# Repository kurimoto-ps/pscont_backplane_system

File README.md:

# pscont_backplane_system

**2マスターのクレート収容案**　[電源8 HP＋コンバータ36 HP＋チョッパ36 HP](backplane_board/mechanical/dual_master_crate/README.md) · [正面図・電源ベイの立体図・容量比較（PDF）](backplane_board/mechanical/dual_master_crate/dual_master_crate.pdf)

**比較元の1マスター機構案**　[6Uクレート・正面左16 HPの着脱式電源](backplane_board/mechanical/front_psu_16hp/README.md) · [3D組立・取付図（PDF）](backplane_board/mechanical/front_psu_16hp/PSCONT_front_PSU_views.pdf)

大型電源の三相PWMコンバータと2象限単相チョッパを制御するシステム。電流制御はSTM32H745XIH6、同期と指令配信は10M16DCF484I7Gで行う。2マスター案では各系統がPWM 6枚とDAC 1枚を担当する。下表のKiCad設計は先行する1マスター版。

| プロジェクト | 内容 |
|---|---|
| [backplane_board](backplane_board/README.md) | 受動バックプレーンの回路設計仕様。96差動対の割当、電源容量、保護、評価項目を含む。 |
| [16 ch DAC・4 HP化と盤内電源の検討](backplane_board/mechanical/dac_4hp/README.md) | 14共通スロット案。負荷別の電力、112対の割当、電源取付と背面保守のPDF・DXF・STEP。 |
| [KiCadプロジェクト](backplane_board/backplane_board.kicad_pro) | KiCad 10。全体結線、12 V保護、6Uマスタの160極2コネクタ、PWM 12スロットの階層回路図。 |
| [スロット結線表](backplane_board/slot_links.csv) | マスタ・スロット間の全96対。電気的に独立する正負ネットと終端位置。 |
| [回路図PDF](backplane_board/backplane_board.pdf) | A3、全22ページ。各スロットの実装部品番号を展開。 |
| [通販URL付きBOM](backplane_board/BOM.csv) | 1台分の購入部品と在庫掲載数。 |

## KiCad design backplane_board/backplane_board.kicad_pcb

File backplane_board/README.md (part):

# バックプレーン基板 回路設計仕様

**4 HPカード・前面着脱式電源の機構案**　[機構仕様・組立図・STEP・寸法DXF](mechanical/front_psu_16hp/README.md)。KiCad基板本体は先行する6 HP版。

[増設検討：16 ch DAC・4 HP共通スロット・電源取付（PDF／DXF／STEP）](mechanical/dac_4hp/README.md)。下のKiCad原図は比較元の12スロット版。

対象はマスタ1枚、三相PWMコンバータ用カード6枚、単相チョッパ用カード6枚を同時に実装できるバックプレーン。カード間の信号配線は受動式で、電源入口に逆接保護MOSFETを実装する。電力は電源入力容量を決めるための設計予算で、実測値・デバイス全動作条件での保証値とは区別する。

[全22ページの回路図PDF](backplane_board.pdf) · [KiCad 10プロジェクト](backplane_board.kicad_pro) · [購入用BOM](BOM.csv) · [端子対応表](slot_links.csv)

[KiCad基板・部品配置](backplane_board.kicad_pcb) · [部品配置と固定方法の図面（PDF 3ページ）](mechanical/placement_review.pdf) · [支持板・補強材の寸法と組付け](mechanical/README.md)

| PDF | 回路 | 接続先 |
|---|---|---|
| 1 | システム結線。1本のバスが16本の実配線を表す | マスタのJ2・J3から12個のPWMソケット |
| 2 | J1、F1、Q1、D1、R1、マスタ分岐F2 | 保護後の12 Vを全13分岐に供給 |
| 3–6 | J2、三相用6枚。3ページは給電・GNDと階層入口、4–6ページは各信号端子 | a列でC1/C2、b列でC3/C4、c列でC5/C6 |
| 7–10 | J3、チョッパ用6枚。7ページは給電・GNDと階層入口、8–10ページは各信号端子 | a列でH1/H2、b列でH3/H4、c列でH5/H6 |
| 11–22 | J11–J22。共通階層を物理スロットごとに展開 | 各48極、固有ヒューズF11–F22、測定点TP11–TP22 |

KiCadではプロジェクト一式を開く。BOMのHARTING型番には先頭にゼロがあるため、表計算ソフトへの取り込み時にMPN列を文字列として扱う。在庫欄には通販ページの掲載数、参照日、掲載情報の経過時間を記載した。

## 1. 実装単位と配線範囲

| 実装場所 | 主な部品・役割 |
|---|---|
| マスタ | STM32H745XIH6、SDRAM、MAX 10 10M16DCF484I7G、LVDS送受信器、基準クロック、トリップ集約・ラッチ。FMC16はSDRAM用。 |
| バックプレーン | マスタスロットM、ドータースロットC1–C6／H1–H6、電源入口と分岐保護、信号GNDと電源帰路。カード間に能動リピータを置かない。ゲート光ファイバは各ドーター前面から引き出す。 |
| PWMカード | STM32G474を仮定。LVDS送受信器、HFBR-1522ETZ×6とLED駆動、HFBR-2522ETZ×6と入力整形、CH別故障ラッチ、光出力禁止回路、ローカルDC/DC。 |

| カード | 動作用の3語 | 自カードが使う指令 | 光PWM出力 |
|---|---|---|---|
| C1–C6 | U, V, W | 全6枚が同じ3語を使用 | 1枚で三相1台分。U上下・V上下・W上下の6出力 |
| H1, H6 | D1, D2, D3 | D1 | 1枚で同一段の最大3パラ、各2出力 |
| H2, H5 | 同上 | D2 | 同上 |
| H3, H4 | 同上 | D3 | 同上 |

6直では電力回路の物理順をH1–H2–H3–中点接地–H4–H5–H6とする。この中点接地は主回路側の接地点。バックプレーンの信号GND／シャーシとの接続は盤の接地設計で別途確定する。使用するスロット・CH・指令語・位相を停止中に確定し、運転中は固定する。

## 2. 信号インターフェース

3.3 V CMOSは各カード内で使用。バックプレーン区間はTIA/EIA-644 LVDS、スター型の一対一配線。各ポートの1出力で1受信端を駆動し、差動配線は公称100 Ω。信号の分岐はLVDS送信器入力側で行う。100 Ω終端は各受信器の直近でP–N間に1個とし、受動バックプレーン上には実装しない。

| スロット当たりの対 | 向き | 用途 |
|---|---|---|
| REFCLK | M→PWM | 連続16 MHz基準。全カード共通。SPI停止中も継続 |
| SYNC | M→PWM | 基準同期のキャリア位相原点。全カード準備後、タイマをハードウェア起動 |
| SCLK | M→PWM | バーストSPIクロック。運転時16 MHz案 |
| CS_N | M→PWM | 運転時は実装対象を同時選択、設定・診断は個別選択 |
| MOSI | M→PWM | 三相用またはチョッパ用。群内同一データ、各スロット専用対 |
| MISO | PWM→M | ポート固有の応答。停止後の診断は2 MHz案 |
| SLOT_OK_N | PWM→M | 正常かつ準備済みで受信論理L、異常／受信Hでトリップ。故障元をスロット単位で識別 |
| RUN_PERMIT_N | M→PWM | 受信Lで運転許可、Hで光点弧禁止。全スロットへ専用線で配る |

最大時は下り72対＋上り24対＝96対・192信号接点。各PWMカードは8対・16信号接点。信号GND、電源、帰路は別枠。全ネットを [slot_links.csv](slot_links.csv) に定義する。未使用スロットにも線を用意し、監視対象は停止中の構成設定で決定する。

### コネクタ・基板の設計条件

| 実装部品 | 物理端子の割当 |
|---|---|
| マスタ J2・J3、HARTING 02021602804 | 各5列×32接点。a/b/c各列にスロット2枚を割り当て、1–16が先のスロット、17–32が次のスロット。各対は隣接する奇数=P、偶数=N。両コネクタのz16・z17をF2後の12 Vへ、残りのz列とd列の全接点をGNDへ結線。合計192信号＋124 GND＋4電源＝320接点 |
| PWM J11–J22、HARTING 09232486825 | 列1–8は順にREFCLK、SYNC、SCLK、CS_N、MOSI、MISO、SLOT_OK_N、RUN_PERMIT_N。a=P、b=N、c=GND。a9/a10=分岐12 V、b9/b10=帰路。残り20接点は予約開放 |
| 入力 J1、Phoenix Contact 1711725 | 部品面・電線挿入口側から左の1番に+12 V、右の2番に0 Vを配線。端子台の脇に極性を表示する |

例として、C1のREFCLKはJ2-a1/a2からJ11-a1/b1へ、H6のRUN_PERMIT_NはJ3-c31/c32からJ22-a8/b8へ接続する。マスタ側とPWM側の端子付番方式が異なるため、両端を端子対応表で指定する。

### マスタ・PWMカード側の嵌合相手

新作カードにはHARTINGのライトアングル・オス、はんだ付けを指定する。マスタオスは性能レベル1、メスはレベル2、PWMは従来通りレベル2。表の数量は12スロットをすべて実装したシステム1台分。

| カード側 | 接続するバックプレーン端子 | カード側の購入型番 | 数量 | 購入先 |
|---|---|---|---:|---|
| マスタ | J2、J3（02021602804） | `02011601101`、har-bus 64、5列×32、ライトアングル | 2個／マスタ1枚 | [DigiKey 1195-1019-ND](https://www.digikey.jp/en/products/detail/harting/02011601101/3179601) |
| PWM | J11–J22（09232486825） | `09231486921`、2C形、3列×16 | 1個／枚、計12個 | [DigiKey 製品ページ](https://www.digikey.jp/en/products/detail/harting/09231486921/3180439) |

マスタ側カードのz16・z17はJ2/J3とも同一の12 V入力へ、全d列と残りのz列はGNDへ接続する。先行接点d1、d2、d31、d32は両コネクタでGNDとなる。[嵌合部品の図面と調達情報](verification/card_connectors.md)

マスタカード側2個の本体長は各94 mm。背面コネクタの配置には2個の中心間隔と端部余白を含める。メス仕様の挿入力上限160 Nを2個分加算した320 Nを支持部の荷重検討に用い、既設クレートのレバー・ガイドと整合を取る。専用スロットの機械キーと電源断での挿抜を前提とする。

- 信号GNDはカード間で連続させる。差動対は同一層・同一参照面を優先し、面分割を跨がない。REFCLKとSYNCのスロット間伝搬差、SCLKとMOSIの相対スキュー、SCLK往路＋MISO復路の余裕を、ドライバ・受信器・コネクタを含めて評価する。
- 差動インピーダンス目標100 Ω ±10%を製造業者と合意し、スタックアップとクーポンで確認。コネクタの差動挿入損失・反射と基板長は、筐体寸法とコネクタ配置決定後に評価。実装側／嵌合側とP/N極性を全スロットで照合する。
- RUN_PERMIT_Nは電源投入・カード電源断・マスタ構成中に点弧禁止となるようカード側でハードウェア処理する。DS90LV048Aの開放時出力Hを利用し、実配線の断線・片線断・ドライバ無給電を個別試験する。単一の静的論理値だけでは固着した正常信号を検出できない。

## 3. LVDS部品数と3.3 V負荷

基準部品は4回路入りのTI DS90LV047A（TX）とDS90LV048A（RX）。下表は**パッケージ単位**で積算。TXは全4回路100 Ω負荷・静止入力で代表20 mA／最大30 mA、RXは入力開放・出力無負荷・有効で代表9 mA／最大15 mA。PWM側の端数チャネルもパッケージ丸ごと計上する。マスタのTXは機能別にまとめ、許可線のOEをデータ線と混載しない。この割付でも18個に収まる。 [TXデータシート](https://www.ti.com/lit/ds/symlink/ds90lv047a.pdf) · [RXデータシート](https://www.ti.com/lit/ds/symlink/ds90lv048a.pdf)

| 場所 | 必要TX／RX回路 | TX／RX個数 | 代表条件での電流 | 静的最大欄での試算 | 3.3 Vでの試算電力 |
|---|---:|---:|---:|---:|---:|
| マスタ1枚 | 72／24 | 18／6 | 414 mA | 630 mA | 2.079 W |
| PWMカード1枚 | 2／6 | 1／2 | 38 mA | 60 mA | 0.198 W |
| PWMカード12枚 | 24／72 | 12／24 | 456 mA | 720 mA | 2.376 W |
| システム合計 | 96／96 | **30／30** | **870 mA** | **1.350 A** | **4.455 W** |

これはLVDS回路への供給電力。TXの負荷付き電流には遠端終端への送出分が含まれる。終端での発熱は代表350 mVなら1対当たり約1.23 mWであり、総電源予算に再加算しない。動作時の出力負荷・周波数・CMOSファンアウト・クロック分配ICの増分は別途電力枠に入れる。96対の終端はいずれもカード上にあり、バックプレーン固有の定常損失は主に電源配線・接点・分岐保護による。

## 4. 光回路とカード電源の予算

**配電案は12 Vをバックプレーンで配り、各カードで必要な電圧へ変換する。** 既設マスタの電源入口・レギュレータ適合は回路図で確認する。12 Vを受けられない場合はマスタ入口に適合する変換段を設け、入力電力を再計算する。以下の割当は変換後の負荷側の値。

| PWMカード1枚の負荷 | 条件 | 設計電流 | 電力 |
|---|---|---:|---:|
| 5 V 光送信LED | HFBR-1522ETZ×6、60 mA/CHで6本同時を給電上の包絡条件とする | 360 mA | 1.80 W |
| 5 V 光受信器 | HFBR-2522ETZ×6、受光時の電源電流最大10 mA/CH（RL開放） | 60 mA | 0.30 W |
| 5 V 光受信出力のプルアップ | 外付けのみを想定。560 Ω候補、抵抗・電圧許容差込み10 mA/CHの枠 | 60 mA | 0.30 W |
| 3.3 V LVDS | 1 TX＋2 RXパッケージ | 60 mA | 0.198 W |
| 3.3 V G474 | 128 MHzタイマ、SPI/DMA動作。シリコン実測前の設計枠 | 150 mA | 0.495 W |
| 3.3 V 補助回路 | 光ドライバの動作電流、ラッチ、レベル変換、クロック、LVDS動的増分などの暫定枠 | 90 mA | 0.297 W |
| 各公称レールの合計 | **5 V 0.48 A、3.3 V 0.30 A** | — | **3.390 W** |

PWMカード1枚のローカル出力負荷枠は**4.0 W**。3.390 Wとの差を電源電圧許容差、光ドライバ・補助回路の増分等に充てる。60 mAはBroadcomのリンク評価に使われた設計仮定。三相の相補駆動で6本が同時に点灯することを意味しない。実ゲートの極性、ケーブル長・光量、駆動回路の消灯時電流およびパルス時の瞬時電流で再評価する。入力の内部プルアップと外付け抵抗の扱いも回路で決める。 [Broadcom HFBR-0500ETZ pp.13–18](https://docs.broadcom.com/doc/AV02-3283EN) · [STM32G474データシート](https://www.st.com/resource/en/datasheet/stm32g474re.pdf)

| マスタの負荷 | 初期割当 | 確定方法 |
|---|---:|---|
| STM32H745XIH6＋SDRAM | 3.0 W | 両コアのクロック、レギュレータ方式、使用ペリフェラル、SDRAMの品番・アクセス率からレール別に再計算 |
| MAX 10 10M16DCF484I7G | 3.0 W | コア・PLL・I/O各レールをEPEで見積もり、実装後にフィット結果とスイッチング率で更新 |
| LVDS送受信器 | 2.079 W | 前表の静的試算。REFCLK常時動作・SPI最大更新で測定 |
| その他 | 1.5 W | クロック分配、CMOS駆動、LVDS動的増分、保護・監視等 |
| 合計・負荷枠 | 9.579 W → **10.0 W** | 部品型番だけではマスタ実消費を決定できない。カードの12 V入力でも検証 |

[STM32H745データシート](https://www.st.com/resource/en/datasheet/DM00600954.pdf) · [Altera MAX 10 電源設計・EPE](https://docs.altera.com/r/docs/683400/18.0/max-10-power-management-user-guide/power-supply-design)

## 5. 12 V配電・接点・保護

カード内の全変換段をまとめた効率下限を85%、カード入力設計下限を10.8 Vと仮定する。マスタと12枚の合計ローカル負荷枠は10＋12×4＝**58 W**。カード入力合計は**68.24 W**、10.8 Vで**6.32 A**。暫定仕様は下表の通り。ファン、外部ゲートドライバ、他の盤内負荷はこの負荷枠の外。

| 項目 | 設計値・判定条件 |
|---|---|
| バックプレーン入力 | 12 V公称、電源端±5%を想定。電源候補は**12 V／10 A（120 W）**。最遠カード実端の電圧を検証する |
| 分岐容量 | PWM **0.50 A／枚**（計算0.436 A）、マスタ **1.25 A**（計算1.089 A）。同時割当合計 **7.25 A**。PWMは1 A、マスタは2 Aの速断ヒューズ |
| 主幹・入口コネクタ | 12 V側および帰路とも周囲温度・多極同時通電のディレーティング後で連続10 A以上。分岐保護素子と電源の電流制限・遮断特性を協調させる |
| 電圧降下 | 7.25 A同時割当時、電源出力端から最遠カード入力まで往復0.30 V以下を配線・接点・保護素子込みの目標とする。電源下限11.4 Vならカード端11.1 V以上。主幹と分岐ごとの共通区間電流で計算 |
| 分岐・計測 | 電源入口の逆接対策と主幹保護、マスタ用1系統＋PWM用12系統の個別ヒューズ等を検討。各分岐に測定点を設ける。電源と帰路の銅箔・ビア・接点を対で設計する |
| 投入・抜去 | 全カード同時起動時の入力容量・突入・ヒューズI²t・電源の電流制限を実測。初版は停止・電源断で挿抜する想定。運転中の予定カード喪失はトリップ |
| 発熱 | 主幹・分岐は区間ごとにI²R、接点は接触抵抗最大値と偏流で算定。電源容量120 Wを基板の発熱として扱わない。最大負荷・想定最高周囲温度で温度上昇を確認する |

### 逆接保護と電圧降下の内訳

Q1はPチャネルで、DをF1出力、Sを保護後の12 Vとする。正接続ではボディダイオードを介してSが上がり、R1がGを引き下げて導通する。D1はカソードをS、アノードをGに接続して負のVGSを約10 Vに制限する。逆極性を無通電状態から加えた場合はボディダイオードが逆バイアスになる。盤の12 V電源を唯一の給電元とする。D1はゲートの保護用で、幹線のサージ耐量は盤電源の条件で評価する。[Infineon Q1 pp.1–2](https://www.infineon.com/assets/row/public/documents/10/49/infineon-ipd90p04p4l-04-datasheet-en.pdf) · [Vishay D1](https://www.vishay.com/docs/86342/bzt52.pdf)

| 区間 | 採用値と負荷 | 電圧降下の目安 |
|---|---|---:|
| 共通F1＋Q1 | 7.25 A × (5.6 mΩ＋6.6 mΩ)。F1は冷抵抗代表値、Q1は25 °C・VGS = −4.5 Vの最大値 | 88.5 mV |
| マスタF2 | 1.25 A × 36.7 mΩ | 45.9 mV |
| PWMヒューズ各1本 | 0.50 A × 78.0 mΩ | 39.0 mV |
| 0.30 V目標の残り | マスタ約166 mV、PWM約173 mVを電源ケーブル、端子、往復銅箔、嵌合接触、温度上昇へ配分 | 実測対象 |

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
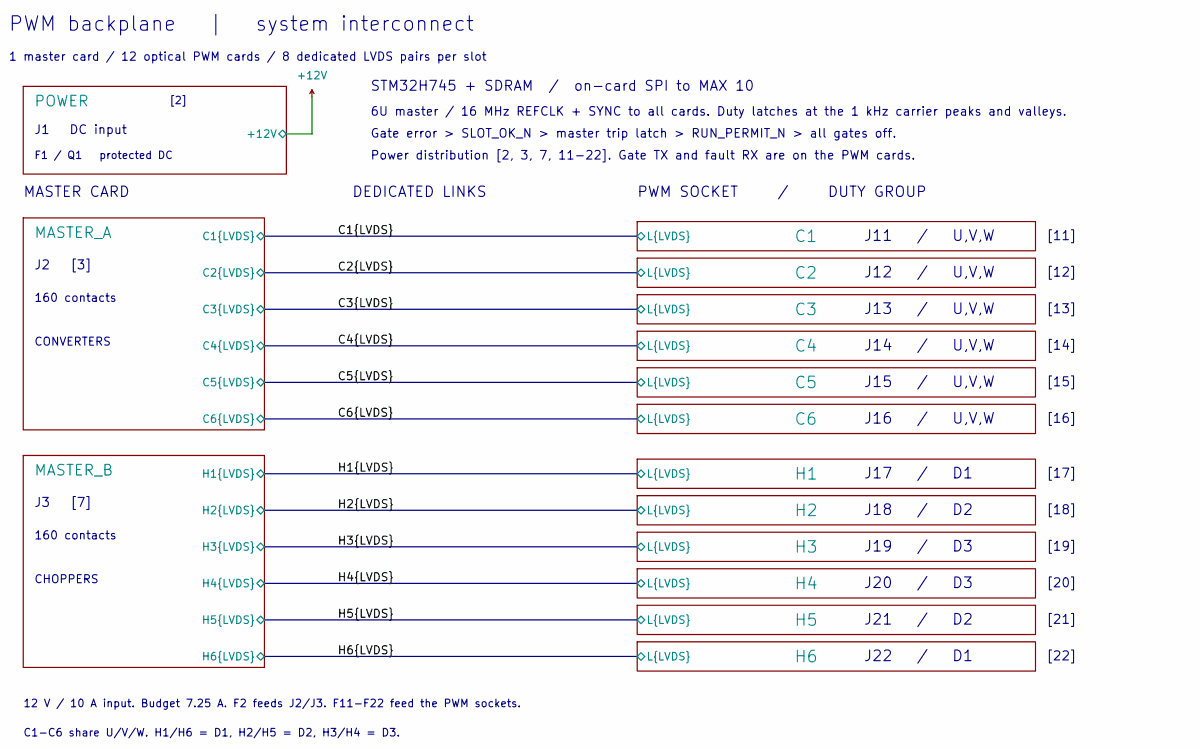
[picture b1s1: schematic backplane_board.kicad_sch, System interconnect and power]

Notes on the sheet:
CONVERTERS
J13 / U,V,W
J22 / D1
J17 / D1
[16]
[18]
J2 [3]
[21]
CHOPPERS
PWM backplane | system interconnect
J18 / D2
[15]
12 V / 10 A input. Budget 7.25 A. F2 feeds J2/J3. F11-F22 feed the PWM sockets.
J19 / D3
STM32H745 + SDRAM / on-card SPI to MAX 10
Power distribution [2, 3, 7, 11-22]. Gate TX and fault RX are on the PWM cards.
DEDICATED LINKS
MASTER CARD
160 contacts
[14]
[17]
[20]
J20 / D3
J15 / U,V,W
J11 / U,V,W
C1-C6 share U/V/W. H1/H6 = D1, H2/H5 = D2, H3/H4 = D3.
Gate error > SLOT_OK_N > master trip latch > RUN_PERMIT_N > all gates off.
1 master card / 12 optical PWM cards / 8 dedicated LVDS pairs per slot
[2]
PWM SOCKET / DUTY GROUP
[22]
[12]
J14 / U,V,W
J16 / U,V,W
J1 DC input
[13]
J21 / D2
F1 / Q1 protected DC
J3 [7]
J12 / U,V,W

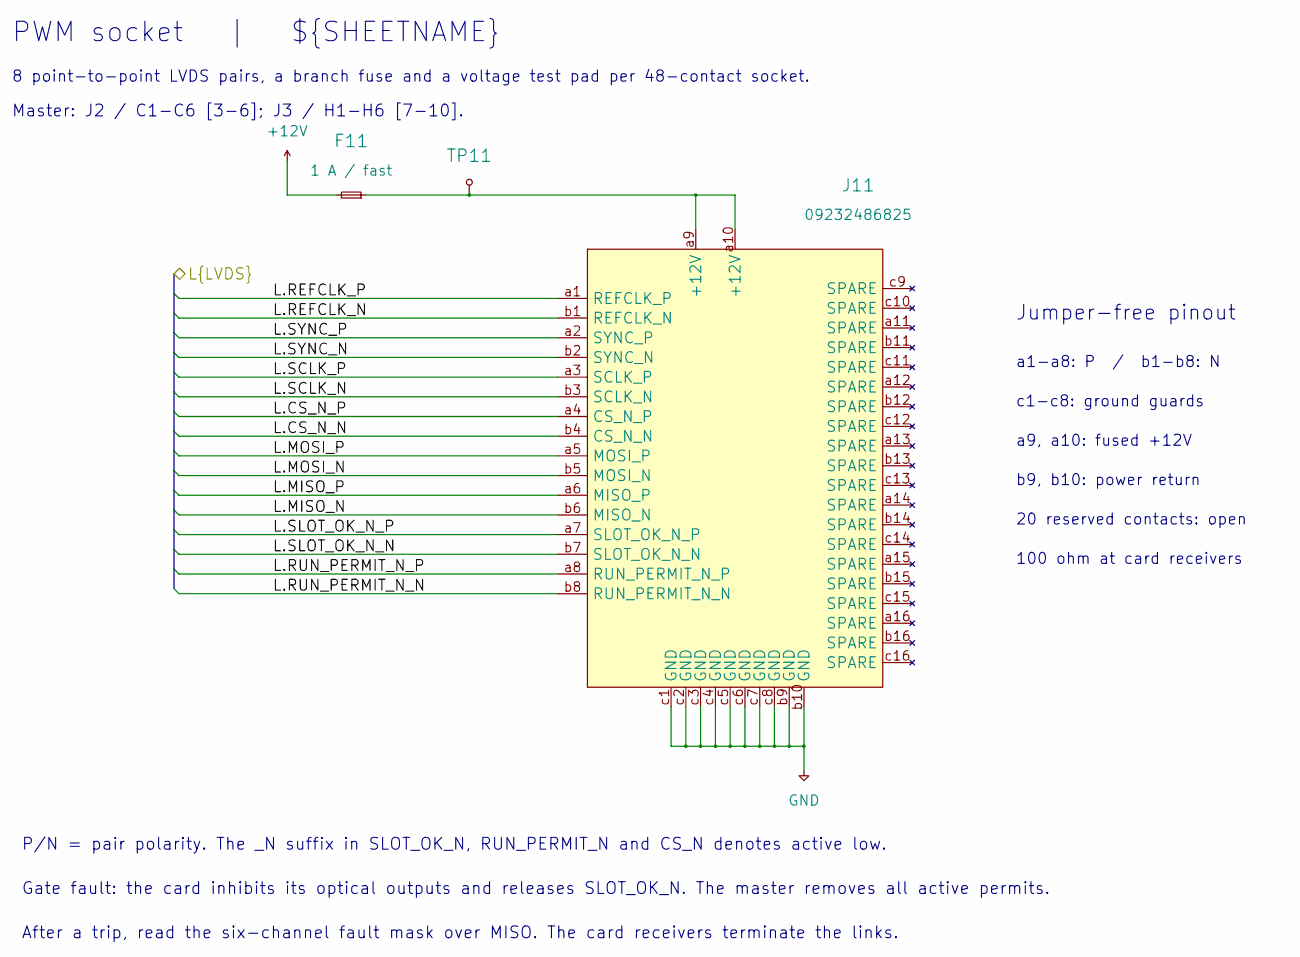
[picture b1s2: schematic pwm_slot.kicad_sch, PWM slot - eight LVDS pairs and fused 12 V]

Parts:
F11: 1 A / fast; Fuse_Littelfuse-NANO2-451_453; MPN 0451001.MRL
J11: 09232486825; DIN41612_C2_3x16_Female_Vertical_THT; MPN 09232486825
TP11: TestPoint; TestPoint_Pad_D2.0mm

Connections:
+12V: F11.1; also elsewhere on the board
/C1.CS_N_N: J11.b4 (CS_N_N); also elsewhere on the board
/C1.CS_N_P: J11.a4 (CS_N_P); also elsewhere on the board
/C1.MISO_N: J11.b6 (MISO_N); also elsewhere on the board
/C1.MISO_P: J11.a6 (MISO_P); also elsewhere on the board
/C1.MOSI_N: J11.b5 (MOSI_N); also elsewhere on the board
/C1.MOSI_P: J11.a5 (MOSI_P); also elsewhere on the board
/C1.REFCLK_N: J11.b1 (REFCLK_N); also elsewhere on the board
/C1.REFCLK_P: J11.a1 (REFCLK_P); also elsewhere on the board
/C1.RUN_PERMIT_N_N: J11.b8 (RUN_PERMIT_N_N); also elsewhere on the board
/C1.RUN_PERMIT_N_P: J11.a8 (RUN_PERMIT_N_P); also elsewhere on the board
/C1.SCLK_N: J11.b3 (SCLK_N); also elsewhere on the board
/C1.SCLK_P: J11.a3 (SCLK_P); also elsewhere on the board
/C1.SLOT_OK_N_N: J11.b7 (SLOT_OK_N_N); also elsewhere on the board
/C1.SLOT_OK_N_P: J11.a7 (SLOT_OK_N_P); also elsewhere on the board
/C1.SYNC_N: J11.b2 (SYNC_N); also elsewhere on the board
/C1.SYNC_P: J11.a2 (SYNC_P); also elsewhere on the board
GND: J11.b9 (GND), J11.b10 (GND), J11.c1 (GND), J11.c2 (GND), J11.c3 (GND), J11.c4 (GND), J11.c5 (GND), J11.c6 (GND), J11.c7 (GND), J11.c8 (GND); also elsewhere on the board
unnamed: F11.2, J11.a9 (+12V), J11.a10 (+12V), TP11.1 (1_1)

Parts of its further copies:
F12, F13, F14, F15, F16, F17, F18, F19, F20, F21, F22: 1 A / fast; Fuse_Littelfuse-NANO2-451_453; MPN 0451001.MRL
J12, J13, J14, J15, J16, J17, J18, J19, J20, J21, J22: 09232486825; DIN41612_C2_3x16_Female_Vertical_THT; MPN 09232486825
TP12, TP13, TP14, TP15, TP16, TP17, TP18, TP19, TP20, TP21, TP22: TestPoint; TestPoint_Pad_D2.0mm

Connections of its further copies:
+12V: F12.1, F13.1, F14.1, F15.1, F16.1, F17.1, F18.1, F19.1, F20.1, F21.1, F22.1; also elsewhere on the board
/C2.CS_N_N: J12.b4 (CS_N_N); also elsewhere on the board
/C2.CS_N_P: J12.a4 (CS_N_P); also elsewhere on the board
/C2.MISO_N: J12.b6 (MISO_N); also elsewhere on the board
/C2.MISO_P: J12.a6 (MISO_P); also elsewhere on the board
/C2.MOSI_N: J12.b5 (MOSI_N); also elsewhere on the board
/C2.MOSI_P: J12.a5 (MOSI_P); also elsewhere on the board
/C2.REFCLK_N: J12.b1 (REFCLK_N); also elsewhere on the board
/C2.REFCLK_P: J12.a1 (REFCLK_P); also elsewhere on the board
/C2.RUN_PERMIT_N_N: J12.b8 (RUN_PERMIT_N_N); also elsewhere on the board
/C2.RUN_PERMIT_N_P: J12.a8 (RUN_PERMIT_N_P); also elsewhere on the board
/C2.SCLK_N: J12.b3 (SCLK_N); also elsewhere on the board
/C2.SCLK_P: J12.a3 (SCLK_P); also elsewhere on the board
/C2.SLOT_OK_N_N: J12.b7 (SLOT_OK_N_N); also elsewhere on the board
/C2.SLOT_OK_N_P: J12.a7 (SLOT_OK_N_P); also elsewhere on the board
/C2.SYNC_N: J12.b2 (SYNC_N); also elsewhere on the board
/C2.SYNC_P: J12.a2 (SYNC_P); also elsewhere on the board
/C3.CS_N_N: J13.b4 (CS_N_N); also elsewhere on the board
/C3.CS_N_P: J13.a4 (CS_N_P); also elsewhere on the board
/C3.MISO_N: J13.b6 (MISO_N); also elsewhere on the board
/C3.MISO_P: J13.a6 (MISO_P); also elsewhere on the board
/C3.MOSI_N: J13.b5 (MOSI_N); also elsewhere on the board
/C3.MOSI_P: J13.a5 (MOSI_P); also elsewhere on the board
/C3.REFCLK_N: J13.b1 (REFCLK_N); also elsewhere on the board
/C3.REFCLK_P: J13.a1 (REFCLK_P); also elsewhere on the board
/C3.RUN_PERMIT_N_N: J13.b8 (RUN_PERMIT_N_N); also elsewhere on the board
/C3.RUN_PERMIT_N_P: J13.a8 (RUN_PERMIT_N_P); also elsewhere on the board
/C3.SCLK_N: J13.b3 (SCLK_N); also elsewhere on the board
/C3.SCLK_P: J13.a3 (SCLK_P); also elsewhere on the board
/C3.SLOT_OK_N_N: J13.b7 (SLOT_OK_N_N); also elsewhere on the board
/C3.SLOT_OK_N_P: J13.a7 (SLOT_OK_N_P); also elsewhere on the board
/C3.SYNC_N: J13.b2 (SYNC_N); also elsewhere on the board
/C3.SYNC_P: J13.a2 (SYNC_P); also elsewhere on the board
/C4.CS_N_N: J14.b4 (CS_N_N); also elsewhere on the board
/C4.CS_N_P: J14.a4 (CS_N_P); also elsewhere on the board
/C4.MISO_N: J14.b6 (MISO_N); also elsewhere on the board
/C4.MISO_P: J14.a6 (MISO_P); also elsewhere on the board
/C4.MOSI_N: J14.b5 (MOSI_N); also elsewhere on the board
/C4.MOSI_P: J14.a5 (MOSI_P); also elsewhere on the board
/C4.REFCLK_N: J14.b1 (REFCLK_N); also elsewhere on the board
/C4.REFCLK_P: J14.a1 (REFCLK_P); also elsewhere on the board
/C4.RUN_PERMIT_N_N: J14.b8 (RUN_PERMIT_N_N); also elsewhere on the board
/C4.RUN_PERMIT_N_P: J14.a8 (RUN_PERMIT_N_P); also elsewhere on the board
/C4.SCLK_N: J14.b3 (SCLK_N); also elsewhere on the board
/C4.SCLK_P: J14.a3 (SCLK_P); also elsewhere on the board
/C4.SLOT_OK_N_N: J14.b7 (SLOT_OK_N_N); also elsewhere on the board
/C4.SLOT_OK_N_P: J14.a7 (SLOT_OK_N_P); also elsewhere on the board
/C4.SYNC_N: J14.b2 (SYNC_N); also elsewhere on the board
/C4.SYNC_P: J14.a2 (SYNC_P); also elsewhere on the board
/C5.CS_N_N: J15.b4 (CS_N_N); also elsewhere on the board
/C5.CS_N_P: J15.a4 (CS_N_P); also elsewhere on the board
/C5.MISO_N: J15.b6 (MISO_N); also elsewhere on the board
/C5.MISO_P: J15.a6 (MISO_P); also elsewhere on the board
/C5.MOSI_N: J15.b5 (MOSI_N); also elsewhere on the board
/C5.MOSI_P: J15.a5 (MOSI_P); also elsewhere on the board
/C5.REFCLK_N: J15.b1 (REFCLK_N); also elsewhere on the board
/C5.REFCLK_P: J15.a1 (REFCLK_P); also elsewhere on the board
/C5.RUN_PERMIT_N_N: J15.b8 (RUN_PERMIT_N_N); also elsewhere on the board
/C5.RUN_PERMIT_N_P: J15.a8 (RUN_PERMIT_N_P); also elsewhere on the board
/C5.SCLK_N: J15.b3 (SCLK_N); also elsewhere on the board
/C5.SCLK_P: J15.a3 (SCLK_P); also elsewhere on the board
/C5.SLOT_OK_N_N: J15.b7 (SLOT_OK_N_N); also elsewhere on the board
/C5.SLOT_OK_N_P: J15.a7 (SLOT_OK_N_P); also elsewhere on the board
/C5.SYNC_N: J15.b2 (SYNC_N); also elsewhere on the board
/C5.SYNC_P: J15.a2 (SYNC_P); also elsewhere on the board
/C6.CS_N_N: J16.b4 (CS_N_N); also elsewhere on the board
/C6.CS_N_P: J16.a4 (CS_N_P); also elsewhere on the board
/C6.MISO_N: J16.b6 (MISO_N); also elsewhere on the board
/C6.MISO_P: J16.a6 (MISO_P); also elsewhere on the board
/C6.MOSI_N: J16.b5 (MOSI_N); also elsewhere on the board
/C6.MOSI_P: J16.a5 (MOSI_P); also elsewhere on the board
/C6.REFCLK_N: J16.b1 (REFCLK_N); also elsewhere on the board
/C6.REFCLK_P: J16.a1 (REFCLK_P); also elsewhere on the board
/C6.RUN_PERMIT_N_N: J16.b8 (RUN_PERMIT_N_N); also elsewhere on the board
/C6.RUN_PERMIT_N_P: J16.a8 (RUN_PERMIT_N_P); also elsewhere on the board
/C6.SCLK_N: J16.b3 (SCLK_N); also elsewhere on the board
/C6.SCLK_P: J16.a3 (SCLK_P); also elsewhere on the board
/C6.SLOT_OK_N_N: J16.b7 (SLOT_OK_N_N); also elsewhere on the board
/C6.SLOT_OK_N_P: J16.a7 (SLOT_OK_N_P); also elsewhere on the board
/C6.SYNC_N: J16.b2 (SYNC_N); also elsewhere on the board
/C6.SYNC_P: J16.a2 (SYNC_P); also elsewhere on the board
/H1.CS_N_N: J17.b4 (CS_N_N); also elsewhere on the board
/H1.CS_N_P: J17.a4 (CS_N_P); also elsewhere on the board
/H1.MISO_N: J17.b6 (MISO_N); also elsewhere on the board
/H1.MISO_P: J17.a6 (MISO_P); also elsewhere on the board
/H1.MOSI_N: J17.b5 (MOSI_N); also elsewhere on the board
/H1.MOSI_P: J17.a5 (MOSI_P); also elsewhere on the board
/H1.REFCLK_N: J17.b1 (REFCLK_N); also elsewhere on the board
/H1.REFCLK_P: J17.a1 (REFCLK_P); also elsewhere on the board
/H1.RUN_PERMIT_N_N: J17.b8 (RUN_PERMIT_N_N); also elsewhere on the board
/H1.RUN_PERMIT_N_P: J17.a8 (RUN_PERMIT_N_P); also elsewhere on the board
/H1.SCLK_N: J17.b3 (SCLK_N); also elsewhere on the board
/H1.SCLK_P: J17.a3 (SCLK_P); also elsewhere on the board
/H1.SLOT_OK_N_N: J17.b7 (SLOT_OK_N_N); also elsewhere on the board
/H1.SLOT_OK_N_P: J17.a7 (SLOT_OK_N_P); also elsewhere on the board
/H1.SYNC_N: J17.b2 (SYNC_N); also elsewhere on the board
/H1.SYNC_P: J17.a2 (SYNC_P); also elsewhere on the board
/H2.CS_N_N: J18.b4 (CS_N_N); also elsewhere on the board
/H2.CS_N_P: J18.a4 (CS_N_P); also elsewhere on the board
/H2.MISO_N: J18.b6 (MISO_N); also elsewhere on the board
/H2.MISO_P: J18.a6 (MISO_P); also elsewhere on the board
/H2.MOSI_N: J18.b5 (MOSI_N); also elsewhere on the board
/H2.MOSI_P: J18.a5 (MOSI_P); also elsewhere on the board
/H2.REFCLK_N: J18.b1 (REFCLK_N); also elsewhere on the board
/H2.REFCLK_P: J18.a1 (REFCLK_P); also elsewhere on the board
/H2.RUN_PERMIT_N_N: J18.b8 (RUN_PERMIT_N_N); also elsewhere on the board
/H2.RUN_PERMIT_N_P: J18.a8 (RUN_PERMIT_N_P); also elsewhere on the board
/H2.SCLK_N: J18.b3 (SCLK_N); also elsewhere on the board
/H2.SCLK_P: J18.a3 (SCLK_P); also elsewhere on the board
/H2.SLOT_OK_N_N: J18.b7 (SLOT_OK_N_N); also elsewhere on the board
/H2.SLOT_OK_N_P: J18.a7 (SLOT_OK_N_P); also elsewhere on the board
/H2.SYNC_N: J18.b2 (SYNC_N); also elsewhere on the board
/H2.SYNC_P: J18.a2 (SYNC_P); also elsewhere on the board
/H3.CS_N_N: J19.b4 (CS_N_N); also elsewhere on the board
/H3.CS_N_P: J19.a4 (CS_N_P); also elsewhere on the board
/H3.MISO_N: J19.b6 (MISO_N); also elsewhere on the board
/H3.MISO_P: J19.a6 (MISO_P); also elsewhere on the board
/H3.MOSI_N: J19.b5 (MOSI_N); also elsewhere on the board
/H3.MOSI_P: J19.a5 (MOSI_P); also elsewhere on the board
/H3.REFCLK_N: J19.b1 (REFCLK_N); also elsewhere on the board
/H3.REFCLK_P: J19.a1 (REFCLK_P); also elsewhere on the board
/H3.RUN_PERMIT_N_N: J19.b8 (RUN_PERMIT_N_N); also elsewhere on the board
/H3.RUN_PERMIT_N_P: J19.a8 (RUN_PERMIT_N_P); also elsewhere on the board
/H3.SCLK_N: J19.b3 (SCLK_N); also elsewhere on the board
/H3.SCLK_P: J19.a3 (SCLK_P); also elsewhere on the board
/H3.SLOT_OK_N_N: J19.b7 (SLOT_OK_N_N); also elsewhere on the board
/H3.SLOT_OK_N_P: J19.a7 (SLOT_OK_N_P); also elsewhere on the board
/H3.SYNC_N: J19.b2 (SYNC_N); also elsewhere on the board
/H3.SYNC_P: J19.a2 (SYNC_P); also elsewhere on the board
/H4.CS_N_N: J20.b4 (CS_N_N); also elsewhere on the board
/H4.CS_N_P: J20.a4 (CS_N_P); also elsewhere on the board
/H4.MISO_N: J20.b6 (MISO_N); also elsewhere on the board
/H4.MISO_P: J20.a6 (MISO_P); also elsewhere on the board
/H4.MOSI_N: J20.b5 (MOSI_N); also elsewhere on the board
/H4.MOSI_P: J20.a5 (MOSI_P); also elsewhere on the board
/H4.REFCLK_N: J20.b1 (REFCLK_N); also elsewhere on the board
/H4.REFCLK_P: J20.a1 (REFCLK_P); also elsewhere on the board
/H4.RUN_PERMIT_N_N: J20.b8 (RUN_PERMIT_N_N); also elsewhere on the board
/H4.RUN_PERMIT_N_P: J20.a8 (RUN_PERMIT_N_P); also elsewhere on the board
/H4.SCLK_N: J20.b3 (SCLK_N); also elsewhere on the board
/H4.SCLK_P: J20.a3 (SCLK_P); also elsewhere on the board
/H4.SLOT_OK_N_N: J20.b7 (SLOT_OK_N_N); also elsewhere on the board
/H4.SLOT_OK_N_P: J20.a7 (SLOT_OK_N_P); also elsewhere on the board
/H4.SYNC_N: J20.b2 (SYNC_N); also elsewhere on the board
/H4.SYNC_P: J20.a2 (SYNC_P); also elsewhere on the board
/H5.CS_N_N: J21.b4 (CS_N_N); also elsewhere on the board
/H5.CS_N_P: J21.a4 (CS_N_P); also elsewhere on the board
/H5.MISO_N: J21.b6 (MISO_N); also elsewhere on the board
/H5.MISO_P: J21.a6 (MISO_P); also elsewhere on the board
/H5.MOSI_N: J21.b5 (MOSI_N); also elsewhere on the board
/H5.MOSI_P: J21.a5 (MOSI_P); also elsewhere on the board
/H5.REFCLK_N: J21.b1 (REFCLK_N); also elsewhere on the board
/H5.REFCLK_P: J21.a1 (REFCLK_P); also elsewhere on the board
/H5.RUN_PERMIT_N_N: J21.b8 (RUN_PERMIT_N_N); also elsewhere on the board
/H5.RUN_PERMIT_N_P: J21.a8 (RUN_PERMIT_N_P); also elsewhere on the board
/H5.SCLK_N: J21.b3 (SCLK_N); also elsewhere on the board
/H5.SCLK_P: J21.a3 (SCLK_P); also elsewhere on the board
/H5.SLOT_OK_N_N: J21.b7 (SLOT_OK_N_N); also elsewhere on the board
/H5.SLOT_OK_N_P: J21.a7 (SLOT_OK_N_P); also elsewhere on the board
/H5.SYNC_N: J21.b2 (SYNC_N); also elsewhere on the board
/H5.SYNC_P: J21.a2 (SYNC_P); also elsewhere on the board
/H6.CS_N_N: J22.b4 (CS_N_N); also elsewhere on the board
/H6.CS_N_P: J22.a4 (CS_N_P); also elsewhere on the board
/H6.MISO_N: J22.b6 (MISO_N); also elsewhere on the board
/H6.MISO_P: J22.a6 (MISO_P); also elsewhere on the board
/H6.MOSI_N: J22.b5 (MOSI_N); also elsewhere on the board
/H6.MOSI_P: J22.a5 (MOSI_P); also elsewhere on the board
/H6.REFCLK_N: J22.b1 (REFCLK_N); also elsewhere on the board
/H6.REFCLK_P: J22.a1 (REFCLK_P); also elsewhere on the board
/H6.RUN_PERMIT_N_N: J22.b8 (RUN_PERMIT_N_N); also elsewhere on the board
/H6.RUN_PERMIT_N_P: J22.a8 (RUN_PERMIT_N_P); also elsewhere on the board
/H6.SCLK_N: J22.b3 (SCLK_N); also elsewhere on the board
/H6.SCLK_P: J22.a3 (SCLK_P); also elsewhere on the board
/H6.SLOT_OK_N_N: J22.b7 (SLOT_OK_N_N); also elsewhere on the board
/H6.SLOT_OK_N_P: J22.a7 (SLOT_OK_N_P); also elsewhere on the board
/H6.SYNC_N: J22.b2 (SYNC_N); also elsewhere on the board
/H6.SYNC_P: J22.a2 (SYNC_P); also elsewhere on the board
GND: J12.b9 (GND), J12.b10 (GND), J12.c1 (GND), J12.c2 (GND), J12.c3 (GND), J12.c4 (GND), J12.c5 (GND), J12.c6 (GND), J12.c7 (GND), J12.c8 (GND), J13.b9 (GND), J13.b10 (GND), J13.c1 (GND), J13.c2 (GND), J13.c3 (GND), J13.c4 (GND), J13.c5 (GND), J13.c6 (GND), J13.c7 (GND), J13.c8 (GND), J14.b9 (GND), J14.b10 (GND), J14.c1 (GND), J14.c2 (GND), J14.c3 (GND), J14.c4 (GND), J14.c5 (GND), J14.c6 (GND), J14.c7 (GND), J14.c8 (GND), J15.b9 (GND), J15.b10 (GND), J15.c1 (GND), J15.c2 (GND), J15.c3 (GND), J15.c4 (GND), J15.c5 (GND), J15.c6 (GND), J15.c7 (GND), J15.c8 (GND), J16.b9 (GND), J16.b10 (GND), J16.c1 (GND), J16.c2 (GND), J16.c3 (GND), J16.c4 (GND), J16.c5 (GND), J16.c6 (GND), J16.c7 (GND), J16.c8 (GND), J17.b9 (GND), J17.b10 (GND), J17.c1 (GND), J17.c2 (GND), J17.c3 (GND), J17.c4 (GND), J17.c5 (GND), J17.c6 (GND), J17.c7 (GND), J17.c8 (GND), J18.b9 (GND), J18.b10 (GND), J18.c1 (GND), J18.c2 (GND), J18.c3 (GND), J18.c4 (GND), J18.c5 (GND), J18.c6 (GND), J18.c7 (GND), J18.c8 (GND), J19.b9 (GND), J19.b10 (GND), J19.c1 (GND), J19.c2 (GND), J19.c3 (GND), J19.c4 (GND), J19.c5 (GND), J19.c6 (GND), J19.c7 (GND), J19.c8 (GND), J20.b9 (GND), J20.b10 (GND), J20.c1 (GND), J20.c2 (GND), J20.c3 (GND), J20.c4 (GND), J20.c5 (GND), J20.c6 (GND), J20.c7 (GND), J20.c8 (GND), J21.b9 (GND), J21.b10 (GND), J21.c1 (GND), J21.c2 (GND), J21.c3 (GND), J21.c4 (GND), J21.c5 (GND), J21.c6 (GND), J21.c7 (GND), J21.c8 (GND), J22.b9 (GND), J22.b10 (GND), J22.c1 (GND), J22.c2 (GND), J22.c3 (GND), J22.c4 (GND), J22.c5 (GND), J22.c6 (GND), J22.c7 (GND), J22.c8 (GND); also elsewhere on the board
unnamed: F12.2, J12.a9 (+12V), J12.a10 (+12V), TP12.1 (1_1)
unnamed: F13.2, J13.a9 (+12V), J13.a10 (+12V), TP13.1 (1_1)
unnamed: F14.2, J14.a9 (+12V), J14.a10 (+12V), TP14.1 (1_1)
unnamed: F15.2, J15.a9 (+12V), J15.a10 (+12V), TP15.1 (1_1)
unnamed: F16.2, J16.a9 (+12V), J16.a10 (+12V), TP16.1 (1_1)
unnamed: F17.2, J17.a9 (+12V), J17.a10 (+12V), TP17.1 (1_1)
unnamed: F18.2, J18.a9 (+12V), J18.a10 (+12V), TP18.1 (1_1)
unnamed: F19.2, J19.a9 (+12V), J19.a10 (+12V), TP19.1 (1_1)
unnamed: F20.2, J20.a9 (+12V), J20.a10 (+12V), TP20.1 (1_1)
unnamed: F21.2, J21.a9 (+12V), J21.a10 (+12V), TP21.1 (1_1)
unnamed: F22.2, J22.a9 (+12V), J22.a10 (+12V), TP22.1 (1_1)

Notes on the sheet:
PWM socket | ${SHEETNAME}
8 point-to-point LVDS pairs, a branch fuse and a voltage test pad per 48-contact socket.
Master: J2 / C1-C6 [3-6]; J3 / H1-H6 [7-10].
P/N = pair polarity. The _N suffix in SLOT_OK_N, RUN_PERMIT_N and CS_N denotes active low.
Jumper-free pinout
a1-a8: P / b1-b8: N
c1-c8: ground guards
a9, a10: fused +12V
b9, b10: power return
20 reserved contacts: open
100 ohm at card receivers
Gate fault: the card inhibits its optical outputs and releases SLOT_OK_N. The master removes all active permits.
After a trip, read the six-channel fault mask over MISO. The card receivers terminate the links.

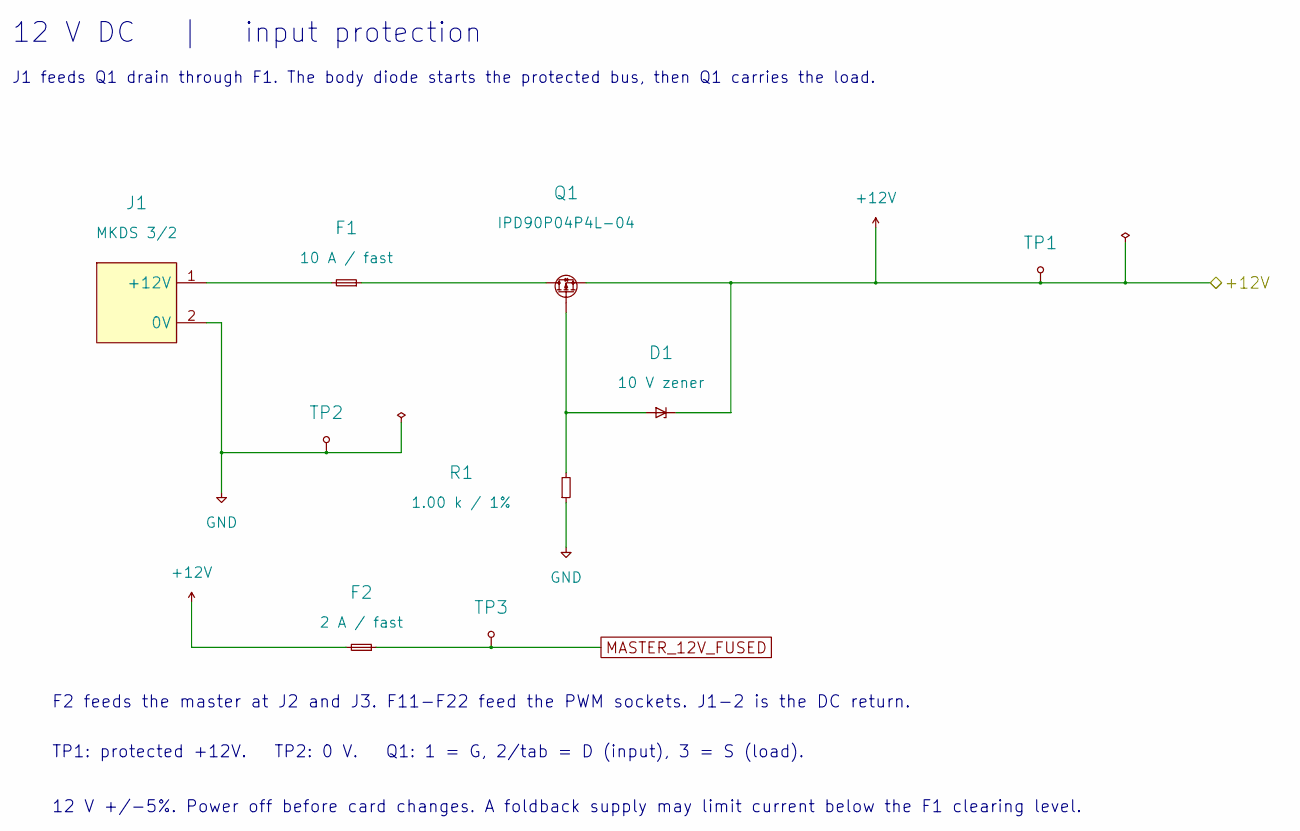
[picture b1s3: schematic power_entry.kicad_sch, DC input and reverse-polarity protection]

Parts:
D1: 10 V zener; BZT52_SOD123; MPN BZT52C10-E3-08
F1: 10 A / fast; Fuse_Littelfuse-NANO2-451_453; MPN 0451010.MRL
F2: 2 A / fast; Fuse_Littelfuse-NANO2-451_453; MPN 0451002.MRL
J1: MKDS 3/2; TerminalBlock_Phoenix_MKDS-3-2-5.08_1x02_P5.08mm_Horizontal; MPN 1711725
Q1: IPD90P04P4L-04; TO-252-2; MPN IPD90P04P4L04ATMA2
R1: 1.00 k / 1%; R_0805_2012Metric; MPN RC0805FR-071KL
TP1, TP2, TP3: TestPoint; TestPoint_Pad_D2.0mm

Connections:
+12V: D1.1 (K), F2.1, Q1.3 (S), TP1.1 (1_1); also elsewhere on the board
GND: J1.2 (0V), R1.2, TP2.1 (1_1); also elsewhere on the board
MASTER_12V_FUSED: F2.2, TP3.1 (1_1); also elsewhere on the board
unnamed: D1.2 (A), Q1.1 (G), R1.1
unnamed: F1.1, J1.1 (+12V)
unnamed: F1.2, Q1.2 (D)

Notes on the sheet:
12 V DC | input protection
J1 feeds Q1 drain through F1. The body diode starts the protected bus, then Q1 carries the load.
F2 feeds the master at J2 and J3. F11-F22 feed the PWM sockets. J1-2 is the DC return.
TP1: protected +12V. TP2: 0 V. Q1: 1 = G, 2/tab = D (input), 3 = S (load).
12 V +/-5%. Power off before card changes. A foldback supply may limit current below the F1 clearing level.

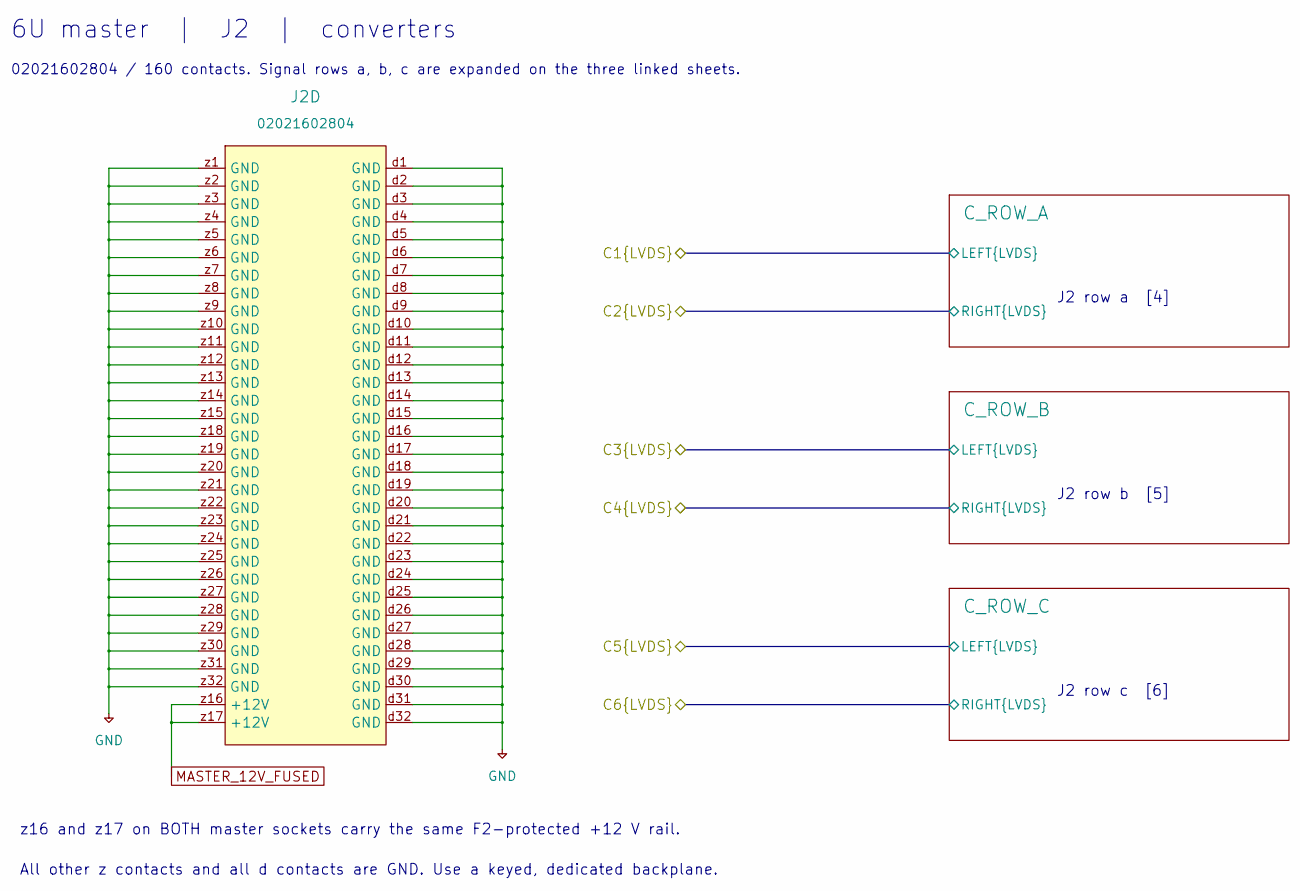
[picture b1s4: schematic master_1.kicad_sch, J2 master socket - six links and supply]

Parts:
J2: 02021602804; HARBUS64_02021602804; MPN 02021602804

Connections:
GND: J2.d1 (GND), J2.d2 (GND), J2.d3 (GND), J2.d4 (GND), J2.d5 (GND), J2.d6 (GND), J2.d7 (GND), J2.d8 (GND), J2.d9 (GND), J2.d10 (GND), J2.d11 (GND), J2.d12 (GND), J2.d13 (GND), J2.d14 (GND), J2.d15 (GND), J2.d16 (GND), J2.d17 (GND), J2.d18 (GND), J2.d19 (GND), J2.d20 (GND), J2.d21 (GND), J2.d22 (GND), J2.d23 (GND), J2.d24 (GND), J2.d25 (GND), J2.d26 (GND), J2.d27 (GND), J2.d28 (GND), J2.d29 (GND), J2.d30 (GND), J2.d31 (GND), J2.d32 (GND), J2.z1 (GND), J2.z2 (GND), J2.z3 (GND), J2.z4 (GND), J2.z5 (GND), J2.z6 (GND), J2.z7 (GND), J2.z8 (GND), J2.z9 (GND), J2.z10 (GND), J2.z11 (GND), J2.z12 (GND), J2.z13 (GND), J2.z14 (GND), J2.z15 (GND), J2.z18 (GND), J2.z19 (GND), J2.z20 (GND), J2.z21 (GND), J2.z22 (GND), J2.z23 (GND), J2.z24 (GND), J2.z25 (GND), J2.z26 (GND), J2.z27 (GND), J2.z28 (GND), J2.z29 (GND), J2.z30 (GND), J2.z31 (GND), J2.z32 (GND); also elsewhere on the board
MASTER_12V_FUSED: J2.z16 (+12V), J2.z17 (+12V); also elsewhere on the board

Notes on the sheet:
6U master | J2 | converters
02021602804 / 160 contacts. Signal rows a, b, c are expanded on the three linked sheets.
J2 row a [4]
J2 row b [5]
J2 row c [6]
z16 and z17 on BOTH master sockets carry the same F2-protected +12 V rail.
All other z contacts and all d contacts are GND. Use a keyed, dedicated backplane.

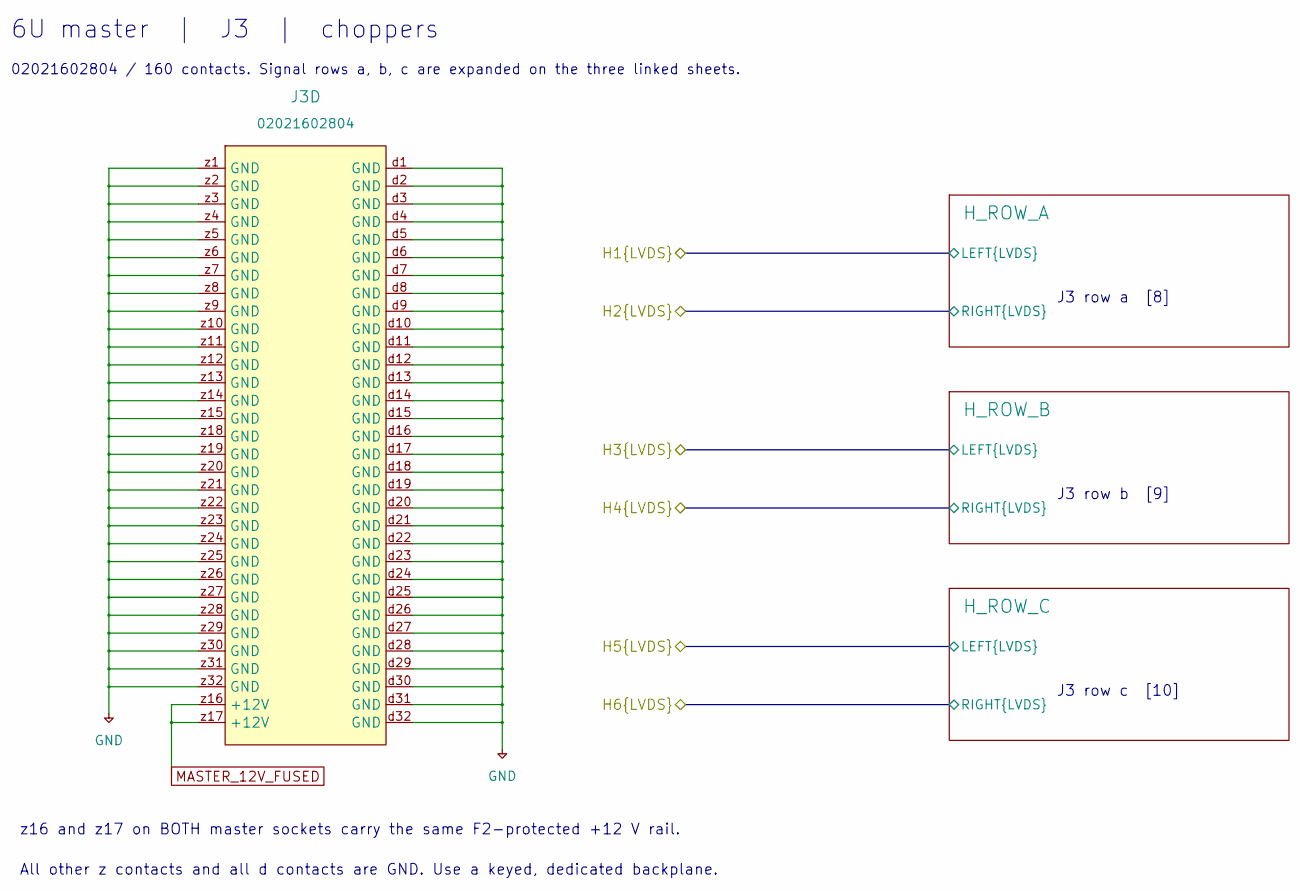
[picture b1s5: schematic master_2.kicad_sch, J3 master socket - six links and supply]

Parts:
J3: 02021602804; HARBUS64_02021602804; MPN 02021602804

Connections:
GND: J3.d1 (GND), J3.d2 (GND), J3.d3 (GND), J3.d4 (GND), J3.d5 (GND), J3.d6 (GND), J3.d7 (GND), J3.d8 (GND), J3.d9 (GND), J3.d10 (GND), J3.d11 (GND), J3.d12 (GND), J3.d13 (GND), J3.d14 (GND), J3.d15 (GND), J3.d16 (GND), J3.d17 (GND), J3.d18 (GND), J3.d19 (GND), J3.d20 (GND), J3.d21 (GND), J3.d22 (GND), J3.d23 (GND), J3.d24 (GND), J3.d25 (GND), J3.d26 (GND), J3.d27 (GND), J3.d28 (GND), J3.d29 (GND), J3.d30 (GND), J3.d31 (GND), J3.d32 (GND), J3.z1 (GND), J3.z2 (GND), J3.z3 (GND), J3.z4 (GND), J3.z5 (GND), J3.z6 (GND), J3.z7 (GND), J3.z8 (GND), J3.z9 (GND), J3.z10 (GND), J3.z11 (GND), J3.z12 (GND), J3.z13 (GND), J3.z14 (GND), J3.z15 (GND), J3.z18 (GND), J3.z19 (GND), J3.z20 (GND), J3.z21 (GND), J3.z22 (GND), J3.z23 (GND), J3.z24 (GND), J3.z25 (GND), J3.z26 (GND), J3.z27 (GND), J3.z28 (GND), J3.z29 (GND), J3.z30 (GND), J3.z31 (GND), J3.z32 (GND); also elsewhere on the board
MASTER_12V_FUSED: J3.z16 (+12V), J3.z17 (+12V); also elsewhere on the board

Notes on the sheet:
6U master | J3 | choppers
02021602804 / 160 contacts. Signal rows a, b, c are expanded on the three linked sheets.
J3 row a [8]
J3 row b [9]
J3 row c [10]
z16 and z17 on BOTH master sockets carry the same F2-protected +12 V rail.
All other z contacts and all d contacts are GND. Use a keyed, dedicated backplane.

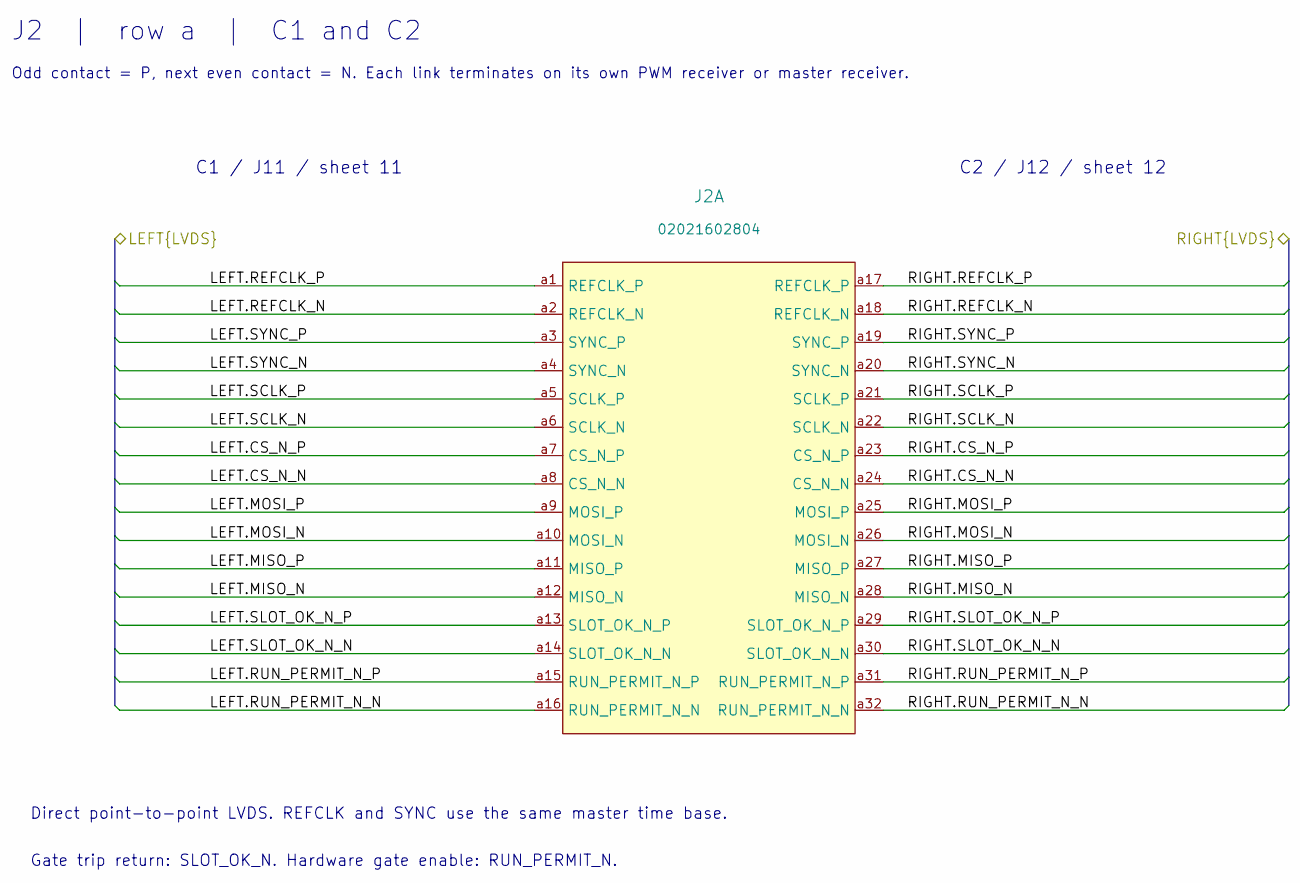
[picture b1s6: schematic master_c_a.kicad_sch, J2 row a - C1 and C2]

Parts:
J2: 02021602804; HARBUS64_02021602804; MPN 02021602804

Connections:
/C1.CS_N_N: J2.a8 (CS_N_N); also elsewhere on the board
/C1.CS_N_P: J2.a7 (CS_N_P); also elsewhere on the board
/C1.MISO_N: J2.a12 (MISO_N); also elsewhere on the board
/C1.MISO_P: J2.a11 (MISO_P); also elsewhere on the board
/C1.MOSI_N: J2.a10 (MOSI_N); also elsewhere on the board
/C1.MOSI_P: J2.a9 (MOSI_P); also elsewhere on the board
/C1.REFCLK_N: J2.a2 (REFCLK_N); also elsewhere on the board
/C1.REFCLK_P: J2.a1 (REFCLK_P); also elsewhere on the board
/C1.RUN_PERMIT_N_N: J2.a16 (RUN_PERMIT_N_N); also elsewhere on the board
/C1.RUN_PERMIT_N_P: J2.a15 (RUN_PERMIT_N_P); also elsewhere on the board
/C1.SCLK_N: J2.a6 (SCLK_N); also elsewhere on the board
/C1.SCLK_P: J2.a5 (SCLK_P); also elsewhere on the board
/C1.SLOT_OK_N_N: J2.a14 (SLOT_OK_N_N); also elsewhere on the board
/C1.SLOT_OK_N_P: J2.a13 (SLOT_OK_N_P); also elsewhere on the board
/C1.SYNC_N: J2.a4 (SYNC_N); also elsewhere on the board
/C1.SYNC_P: J2.a3 (SYNC_P); also elsewhere on the board
/C2.CS_N_N: J2.a24 (CS_N_N); also elsewhere on the board
/C2.CS_N_P: J2.a23 (CS_N_P); also elsewhere on the board
/C2.MISO_N: J2.a28 (MISO_N); also elsewhere on the board
/C2.MISO_P: J2.a27 (MISO_P); also elsewhere on the board
/C2.MOSI_N: J2.a26 (MOSI_N); also elsewhere on the board
/C2.MOSI_P: J2.a25 (MOSI_P); also elsewhere on the board
/C2.REFCLK_N: J2.a18 (REFCLK_N); also elsewhere on the board
/C2.REFCLK_P: J2.a17 (REFCLK_P); also elsewhere on the board
/C2.RUN_PERMIT_N_N: J2.a32 (RUN_PERMIT_N_N); also elsewhere on the board
/C2.RUN_PERMIT_N_P: J2.a31 (RUN_PERMIT_N_P); also elsewhere on the board
/C2.SCLK_N: J2.a22 (SCLK_N); also elsewhere on the board
/C2.SCLK_P: J2.a21 (SCLK_P); also elsewhere on the board
/C2.SLOT_OK_N_N: J2.a30 (SLOT_OK_N_N); also elsewhere on the board
/C2.SLOT_OK_N_P: J2.a29 (SLOT_OK_N_P); also elsewhere on the board
/C2.SYNC_N: J2.a20 (SYNC_N); also elsewhere on the board
/C2.SYNC_P: J2.a19 (SYNC_P); also elsewhere on the board

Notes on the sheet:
J2 | row a | C1 and C2
Odd contact = P, next even contact = N. Each link terminates on its own PWM receiver or master receiver.
C1 / J11 / sheet 11
C2 / J12 / sheet 12
Direct point-to-point LVDS. REFCLK and SYNC use the same master time base.
Gate trip return: SLOT_OK_N. Hardware gate enable: RUN_PERMIT_N.
